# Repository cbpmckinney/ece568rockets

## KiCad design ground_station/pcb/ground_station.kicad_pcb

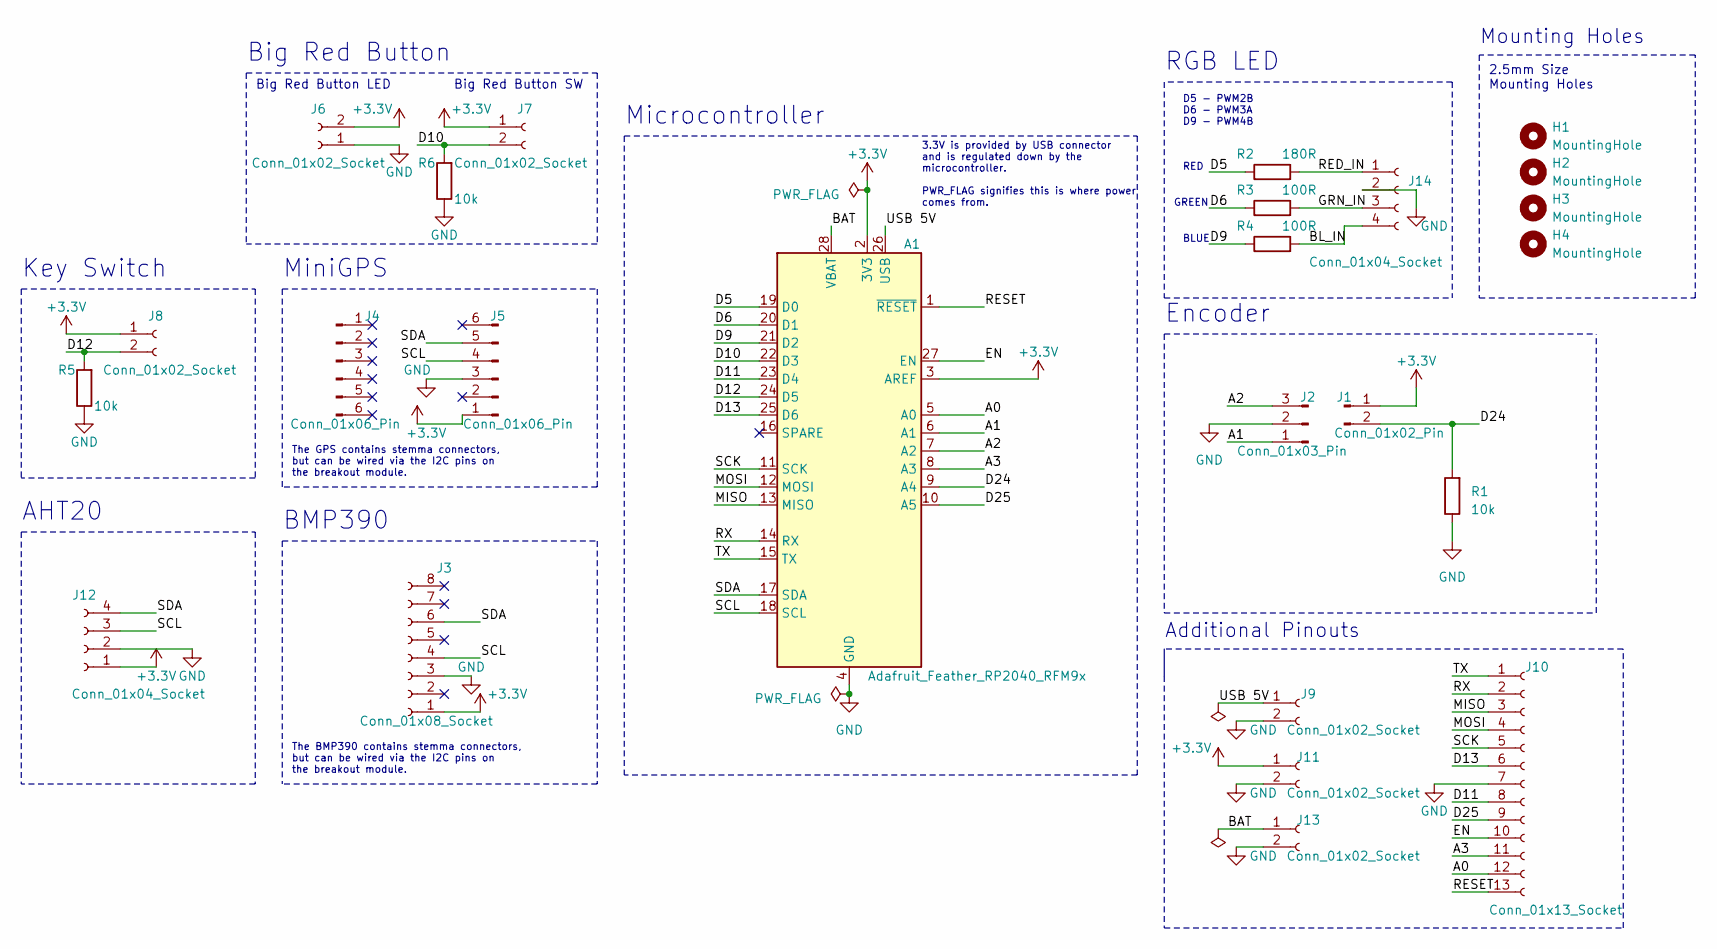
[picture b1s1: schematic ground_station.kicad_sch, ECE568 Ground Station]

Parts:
A1: Adafruit_Feather_RP2040_RFM9x; Adafruit_Feather
H1, H2, H3, H4: MountingHole; MountingHole_2.5mm
J1: Conn_01x02_Pin; PinHeader_1x02_P2.54mm_Vertical
J2: Conn_01x03_Pin; PinHeader_1x03_P2.54mm_Vertical
J3: Conn_01x08_Socket; PinSocket_1x08_P2.54mm_Vertical
J4, J5: Conn_01x06_Pin; PinHeader_1x06_P2.54mm_Vertical
J6, J7, J8, J9, J11, J13: Conn_01x02_Socket; PinSocket_1x02_P2.54mm_Vertical
J10: Conn_01x13_Socket; PinSocket_1x13_P2.54mm_Vertical
J12, J14: Conn_01x04_Socket; PinSocket_1x04_P2.54mm_Vertical
R1, R5, R6: 10k; R_Axial_DIN0309_L9.0mm_D3.2mm_P2.54mm_Vertical
R2: 180R; R_Axial_DIN0309_L9.0mm_D3.2mm_P2.54mm_Vertical
R3, R4: 100R; R_Axial_DIN0309_L9.0mm_D3.2mm_P2.54mm_Vertical

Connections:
+3.3V: A1.2 (3V3), A1.3 (AREF), J1.1, J3.1, J5.1, J6.2, J7.1, J8.1, J11.1, J12.1
/A0: A1.5 (A0), J10.12
/A1: A1.6 (A1), J2.1
/A2: A1.7 (A2), J2.3
/A3: A1.8 (A3), J10.11
/BAT: A1.28 (VBAT), J13.1
/BL_IN: J14.4, R4.2
/D5: A1.19 (D0), R2.1
/D6: A1.20 (D1), R3.1
/D9: A1.21 (D2), R4.1
/D10: A1.22 (D3), J7.2, R6.2
/D11: A1.23 (D4), J10.8
/D12: A1.24 (D5), J8.2, R5.2
/D13: A1.25 (D6), J10.6
/D24: A1.9 (A4), J1.2, R1.2
/D25: A1.10 (A5), J10.9
/EN: A1.27 (EN), J10.10
/GRN_IN: J14.3, R3.2
/MISO: A1.13 (MISO), J10.3
/MOSI: A1.12 (MOSI), J10.4
/RED_IN: J14.1, R2.2
/RESET: A1.1 (~RESET), J10.13
/RX: A1.14 (RX), J10.2
/SCK: A1.11 (SCK), J10.5
/SCL: A1.18 (SCL), J3.4, J5.4, J12.3
/SDA: A1.17 (SDA), J3.6, J5.5, J12.4
/TX: A1.15 (TX), J10.1
/USB 5V: A1.26 (USB), J9.1
GND: A1.4 (GND), J2.2, J3.3, J5.3, J6.1, J9.2, J10.7, J11.2, J12.2, J13.2, J14.2, R1.1, R5.1, R6.1

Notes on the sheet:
The GPS contains stemma connectors, but can be wired via the I2C pins on the breakout module.
Additional Pinouts
Big Red Button LED
RGB LED
2.5mm Size Mounting Holes
Encoder
Microcontroller
3.3V is provided by USB connector and is regulated down by the microcontroller. PWR_FLAG signifies this is where power comes from.
The BMP390 contains stemma connectors, but can be wired via the I2C pins on the breakout module.
Mounting Holes
Big Red Button
AHT20
Key Switch
BMP390
RED
GREEN
BLUE
Big Red Button SW
MiniGPS
D5 - PWM2B D6 - PWM3A D9 - PWM4B

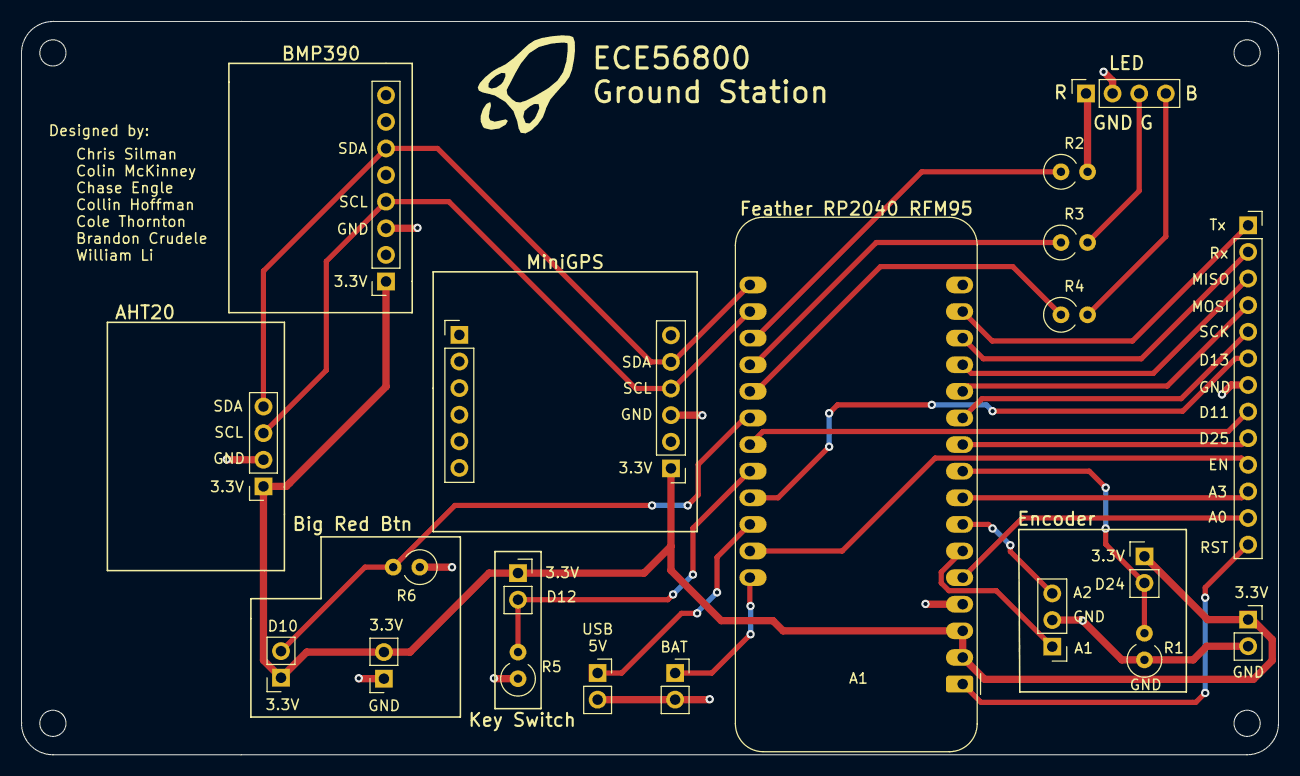
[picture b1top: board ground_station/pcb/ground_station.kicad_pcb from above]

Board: 2 copper layers, 120.0 x 70.0 mm, 25 parts (0 on the bottom side), 29 nets.

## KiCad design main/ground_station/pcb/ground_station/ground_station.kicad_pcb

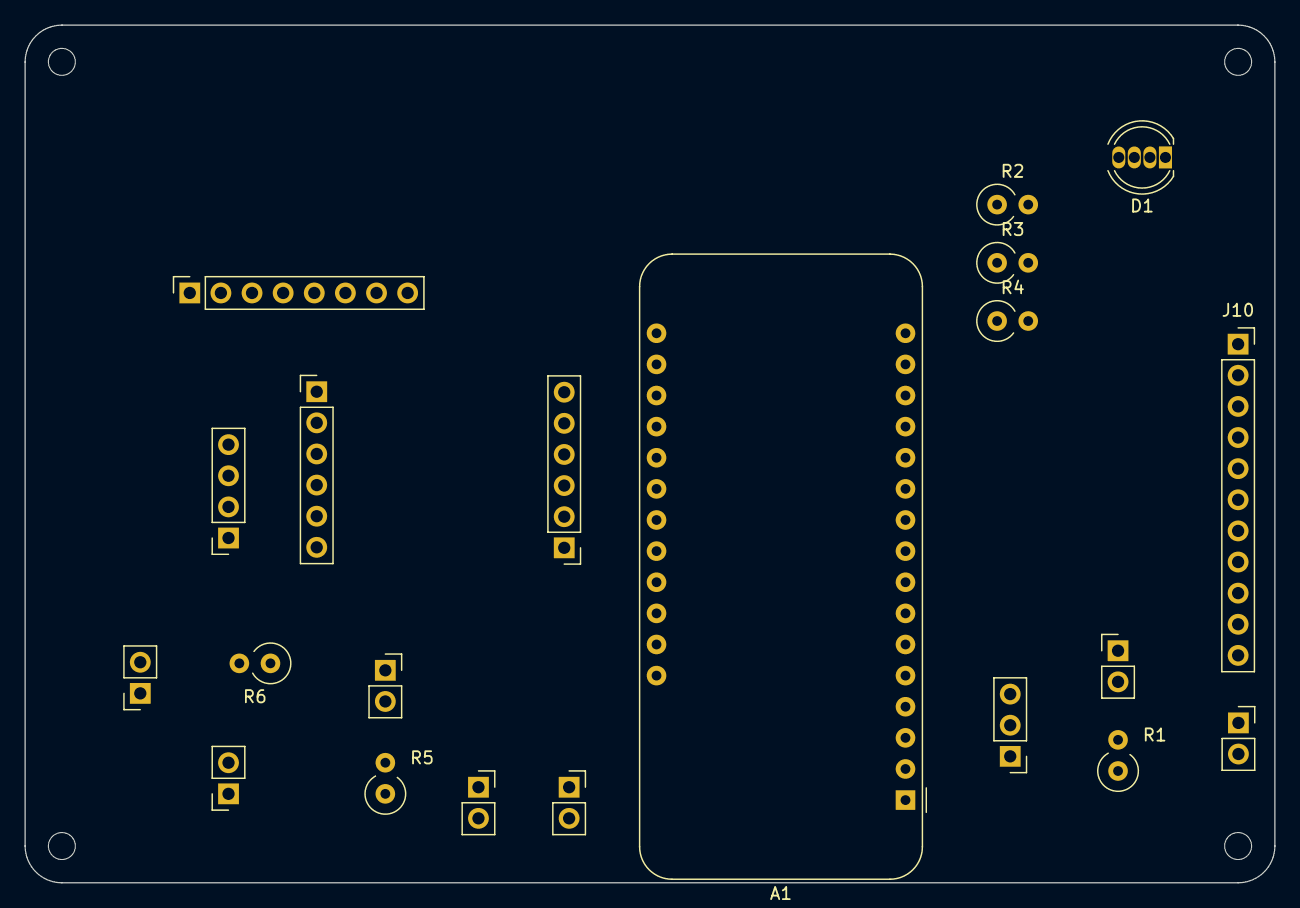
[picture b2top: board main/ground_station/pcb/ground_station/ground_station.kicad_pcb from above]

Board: 2 copper layers, 102.0 x 70.0 mm, 25 parts (0 on the bottom side), 28 nets, no tracks yet.

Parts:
A1: Adafruit_Feather_RP2040_RFM9x; Adafruit_Feather
D1: LED_BGAR; LED_D5.0mm-4_RGB
H1, H2, H3, H4: MountingHole; MountingHole_2.2mm_M2
J1: Conn_01x02_Pin; PinHeader_1x02_P2.54mm_Vertical
J2: Conn_01x03_Pin; PinHeader_1x03_P2.54mm_Vertical
J3: Conn_01x08_Socket; PinSocket_1x08_P2.54mm_Vertical
J4, J5: Conn_01x06_Pin; PinHeader_1x06_P2.54mm_Vertical
J6, J7, J8, J9, J11, J13: Conn_01x02_Socket; PinSocket_1x02_P2.54mm_Vertical
J10: Conn_01x11_Socket; PinSocket_1x11_P2.54mm_Vertical
J12: Conn_01x04_Socket; PinSocket_1x04_P2.54mm_Vertical
R1, R5, R6: 10k; R_Axial_DIN0309_L9.0mm_D3.2mm_P2.54mm_Vertical
R2: 180R; R_Axial_DIN0309_L9.0mm_D3.2mm_P2.54mm_Vertical
R3, R4: 100R; R_Axial_DIN0309_L9.0mm_D3.2mm_P2.54mm_Vertical

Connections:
+3.3V: A1.2 (3V3), A1.3 (3V3), J1.1, J3.1, J5.1, J7.1, J8.1, J11.1, J12.1
/A0: A1.5 (A0), J10.11
/A1: A1.6 (A1), J2.1
/A2: A1.7 (A2), J2.3
/A3: A1.8 (A3), J10.8
/BAT: A1.28 (VBAT), J13.1
/D5: A1.19 (D5), R2.1
/D6: A1.20 (D6), R3.1
/D9: A1.21 (D9), R4.1
/D10: A1.22 (D10), J7.2, R6.2
/D11: A1.23 (D11), J6.2
/D12: A1.24 (D12), J8.2, R5.2
/D13: A1.25 (D13), J10.9
/D24: A1.9 (D24), J1.2, J10.10, R1.2
/EN: A1.27 (EN), J10.2
/MISO: A1.13 (MISO), J10.5
/MOSI: A1.12 (MOSI), J10.6
/RESET: A1.1 (~RESET), J10.1
/RX: A1.14 (RX), J10.4
/SCK: A1.11 (SCK), J10.7
/SCL: A1.18 (SCL), J3.4, J5.4, J12.3
/SDA: A1.17 (SDA), J3.6, J5.5, J12.4
/TX: A1.15 (TX), J10.3
/USB 5V: A1.26 (USB), J9.1
GND: A1.4 (GND), D1.3 (A), J2.2, J3.3, J5.3, J6.1, J9.2, J11.2, J12.2, J13.2, R1.1, R5.1, R6.1
unnamed: D1.1 (BK), R4.2
unnamed: D1.2 (GK), R3.2
unnamed: D1.4 (RK), R2.2

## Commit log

2025-03-17 Initial commit of file structure idea
2025-03-21 Added basic 'Hello World' test that tests the connection of the two screens connected to the RP2040 Feather.
2025-03-21 Fixed file structure
2025-03-21 Initial test file for the OLED screens. Tests having two screens of different addresses by putting Hello World comments on each
2025-03-21 Removed old file structure for project
2025-03-21 Initial commit of OLEDManager header and implementation files
2025-03-22 Added initial files and framework of the classes for OLED
2025-03-22 Actual working build, and set up auxillary class to put text on one of the OLEDs
2025-03-24 Added the foundation for screen manipulation, still missing major components but most functions even if empty are present
2025-03-24 Altered file structure
2025-03-24 Altered file structure again
2025-03-24 Updated commenting to help give better clarity to viewers
2025-03-24 Updated comments
2025-03-24 Added code for pointing to the menu options
2025-03-25 Added start of receiving encoder press
2025-03-25 Changed naming convention from SelectionIndex to CursorIndex as I believe it is clearer
2025-03-26 Cursor currently broken, however, controlling screen jumps should be very easy with the current method. Drawing the cursor in the correct spot is the next difficult challenge.
2025-03-26 PHAT test code
    Integrated elements from two Adafruit samples to test PHAT capabilities.
    Both the pressure and humidity sensors can do temperature sensing, and results from both are very close together. Altitude calculation using standard sea level pressure of 1013.25 seems to undercalcu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
2025-03-27 initial commit for flight computer ino file and sensor class
2025-03-28 Implemented more concrete cursor and screen jumping functionalty to OLED class. Should be much easier to scale to multiple screens. Non-screen jump functionality not implemented yet (i.e. selecting o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
2025-03-28 Updated file structure, cleaned up comments and information, standardized files to each .h and .cpp only correlates to one class
2025-03-28 Further comment cleanup and made drawCentreString method private
2025-03-28 Added LAUNCH_WAIT screen
2025-03-29 Added inputing pin functionality. Need to shrink duplicate code
2025-03-29 We will want this debug code urgently
2025-03-29 Finished out LAUNCH_SEQ page allowing user to submit pin. Protection control is expected outside OLED class.
2025-03-29 more progress
2025-03-29 Bad practice but doing anyway
2025-03-29 Added incorrect pin screen when pin is entered incorrectly
2025-03-29 Added red button launch screen
2025-03-29 Moved tests to different files, fixed index issues with pin inserting, added comments to better clarity
2025-03-29 Added auxillary data screen functionality
2025-03-29 Added capability to reset indices for testing purposes
2025-03-29 This works very well for collecting all the data that we want on the DOF sensor
2025-03-29 add comments
2025-03-29 Rotary test
    Added rotary encoder test
    Does not currently support the push button, only the rotary part.
    Very glitchy.
2025-03-29 Started fleshing out main
2025-03-29 Added encoder test
2025-03-30 Added encoder functionality
2025-03-30 Cleaned up code a bit (much more to do) and set up encoder to connect inputs to screen
2025-03-30 Fixed encoder not properly being sent to mainscreen, should be much smoother now
2025-03-30 Implemented encoder button press
2025-03-31 Cleaned up more comments
2025-03-31 Ignition system test v1
    Initial code for interrupt based arm switch, LED for button, relay, and button.
    For testing I used an LED in place of the relay.
2025-03-31 GPS Hello World Init
2025-03-31 GPS Test File Struct
2025-04-01 Finalized most OLED functionality, fleshed out main.ino
2025-04-01 Fixed some compilation errors
2025-04-02 Update radio_tx.ino
    RHReliableDatagram "Hello World" TX
2025-04-04 Corrected spelling of Auxiliary
2025-04-04 Fixed auxiliary spelling in main as well
2025-04-04 Initial PCB design
2025-04-04 Saved files and pushed again
2025-04-05 Everything working no debug code left I believe
2025-04-07 Changed directory structure
2025-04-07 Updated file structure
2025-04-07 Removed PCB stuff from branch
2025-04-07 GPS Lat & Lon Data
2025-04-07 Quick Fetch: fetch_gps() func.
2025-04-07 Dir org
2025-04-07 Added peripheral inputs for button and key switch as well as LED control
2025-04-08 Added initial relay code to flight computer
2025-04-08 Added RF code to listen for ARM and LAUNCH.
2025-04-10 RF Ground Functions
2025-04-10 RF Rocket Functions
2025-04-10 Fix Incomplete ACK Bug
2025-04-11 Added RF code for ARM/PRIME
2025-04-11 Completed tracing work
2025-04-11 Adds the RF bones for the flight computer
2025-04-11 more stuff
2025-04-12 Pushed manufacturing files
2025-04-14 Added Ground V2 with RF that sorta works...maybe.
2025-04-14 Added RF to main.ino state machine
2025-04-14 Code cleanup
2025-04-14 Fix /tests DIR
2025-04-14 Add GPS & RF Initial Tests
2025-04-15 Removed library files from branch
2025-04-15 Adjust LAUNCH and FLIGHT Cases
2025-04-15 This should fix the altitude code and add some useful debugging tools to the repo
2025-04-16 Copied files from newground
2025-04-16 Fixed compilation issues
2025-04-16 Removed newground directory
2025-04-16 Updated altitudeSensor files
2025-04-16 Removed sensor files temporarily, just working on getting RF situated
2025-04-17 Re-added additional files as radio doesn't work without them. Removed some print statements
2025-04-17 Fixed RFManager.init() being commented out
    Not to name names, but...
2025-04-18 First commit with reading local data sensors
2025-04-18 Initial data storage system implemented
2025-04-18 Added displaying of local data
2025-04-18 Fixed screen updated even when it is not the screen displaying
2025-04-18 Working version of the data display screen with most local data
2025-04-19 Cleaned up prints, cleaned up debug, fixed some issues and corrected screen displaying
2025-04-19 Cleaned up more print statements, added a few comments
2025-04-19 Got lots of RF code working on ground side
    Awesome stuff
2025-04-20 Create temp
2025-04-20 creating CAD rocket sub folder
2025-04-20 Create CAD ground station
2025-04-20 Added ground station files
2025-04-20 Added CAD rocket files
2025-04-20 Adding print images
2025-04-20 3d print images
2025-04-21 Relay stuff
    Added one shot interrupt based timer so the relay will turn off after 5 seconds or when the rocket moves into flight, whichever comes first
2025-04-21 Updated code
    Had to disable some of Chris' state switching override code and go back to the manual version, because of RF and the ACK packets. Basically the radio buffer would get confused if we weren't checking 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
    Functionality with the actual button, rotary encoder, etc. was a little finicky, and occasionally the board seems to lock up when switching states (screen code?). It might also just be the wiring mes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
    I think we may be missing pinMode() calls in setup().
    So far the rocket can (if ground test override applied) make it
2025-04-21 Added functions for GPS transmission
    GPS now sorta works on flight and ground. When in recovery, flight periodically sends GPS data to ground over RF.
    Needs more testing.
2025-04-22 Update main.ino
    Removed auto-switch to RECOVERY for now
2025-04-25 Flight test updates
    Changed to flight mode, not test on ground. Uncommented out transition code needed. Added some printing statements for testing
2025-04-25 Swapped OLED screen addresses and updated GPS lat and long to have properly display coordinates with reduced decimal places
2025-04-25 Reset functions and ignition failure logic
    Added reboot() function and worked on a lot of RF/other stuff for ground/flight to recognize and handle ignition failures/reset commands
2025-04-26 Work
    Working on ground station to use actual key and pin, and rocket side to send SAFE message once per second
2025-04-26 Added some debugging for mainscreen pin behavior
2025-04-26 Minor change on flight
2025-04-26 Commented out test code
2025-04-26 Added key check to ARM state
2025-04-26 Fixed PIN issue
    Fixed PIN issue and also made it so that RTL packet isn't spammed to the rocket
2025-04-26 Minor updates
    Finished with this mostly, ready to pull to dev
2025-04-27 Update main.ino
    Added re-start of serial to recovery mode
2025-04-28 Updates for flight testing
    Added bool to altitude sensor so peak pressure is actually min pressure. Verified with Chase that code is configured for live testing.
2025-05-06 Added OpenRocket design file
